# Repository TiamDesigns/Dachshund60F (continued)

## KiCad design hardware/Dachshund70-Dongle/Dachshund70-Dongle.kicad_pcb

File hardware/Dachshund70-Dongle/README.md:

# Dachshund70 2.4 GHz dongle

The receiver for the keyboard's 2.4 GHz mode (SPEC phase 14). It is a small desk puck: a USB-C cable
runs to the computer, and the puck sits on the desk near the keyboard. KiCad 10, 2 layers, 1.6 mm.

Pins come from the `dongle` section of `boards/Dachshund70/board.json`, as for the keyboard.

## Board

- 40 × 24 mm, 2 mm corners. Two unplated M2 holes, both at the USB end, so no screws sit near the antenna.
- **U2, Raytac MDBT50Q-P1MV2:** the same nRF52840 module as the keyboard, with a certified PCB antenna.
  The antenna end sits 0.4 mm inside the right edge. A keep-out covers the whole strip from the antenna
  to the edge, across the full board width, on both layers: no copper, pour or vias there.
- **J1, USB-C (HRO TYPE-C-31-M-12):** the same part as the keyboard's daughterboard. It is on the left
  edge, at the opposite end from the antenna. USB 2.0 sink: 5.1 kΩ Rd on CC1 and CC2, no PD.
- **Protection:** U1 USBLC6-2SC6 ESD clamp on D+, D− and VBUS; F1 750 mA PTC on VBUS. FB1 ties the
  receptacle shell to GND (the daughterboard does the same).
- **Power:** VBUS feeds both the module's VBUS and VDDH pins (high-voltage mode). VDD (REGOUT0) is +3V3.
  DCCH is unconnected, so REG0 runs as an LDO. There is no 32.768 kHz crystal, so firmware uses the
  internal RC oscillator. Decoupling: 4.7 µF + 100 nF on VBUS/VDDH (C1, C2) and on VDD (C3, C4).
- **User parts:**
  - SW1 PAIR: P1.06, active low.
  - SW2 RESET: P0.18.
  - D1: RGB status LED, common anode on +3V3. Red P0.08 through 1 kΩ; green P1.09 and blue P0.12
    through 330 Ω. All active low, about 1–2 mA each at standard drive.
  - The buttons sit along the top edge, with RESET on the left.
- **J2, SWD:** a 1×5 1.27 mm header in the keyboard's pin order: 1 VDD, 2 SWDIO, 3 SWDCLK, 4 nRESET,
  5 GND. Pin 1 is the probe's voltage reference. Power the dongle from USB while debugging.
- **PCA10059 compatibility:** the button and LED pins match Nordic's nRF52840 Dongle. The dongle
  firmware can be developed on a PCA10059, and the existing `nrf52840dongle/nrf52840` build target
  drives the same button and LEDs. Adafruit's `pca10059` UF2 bootloader uses P1.06 as its DFU button
  and P0.12 as an LED, so it should run here unchanged: hold PAIR while plugging in to get the UF2
  drive. This hasn't been tried yet.

### Routing

- **D+/D−:** routed by hand from U1 to the module as a side-by-side pair, about 23.5 mm each, on F.Cu
  over the B.Cu ground plane. The pair approaches the module pads from below.
- **USB-C fan-out:** no vias on the data lines. The two D+ pads are joined by a short loop under the
  receptacle body, and the two D− pads just behind the pads. U1 is flow-through: each line runs
  straight under the package between its two I/O pins.
- **Supplies:** short straight tracks, hand-routed and locked: +3V3 from C3/C4 into VDD; VDDH down to
  the VBUS row from C1/C2.
- **Everything else:** Freerouting 2.5.0, then GND pours on both layers and stitching vias. B.Cu is
  almost entirely ground.
- **Checks (kicad-cli):** ERC 0. DRC: 0 errors, 0 unconnected items, 0 schematic parity issues. Two
  warnings remain: the stock receptacle footprint's silkscreen runs past the board edge, the same as
  on the daughterboard.
- **Pin check:** a script compared every module pad with `board.json` and followed each net to its
  button, LED, resistor, SWD or USB pin: 0 mismatches.
- One +3V3 track runs on B.Cu under the D+/D− pair on its way to J2. At 12 Mbit/s this doesn't
  matter, but a re-spin could move it.

## Polling rate: 1000 Hz

The nRF52840's USB peripheral is **full speed only (12 Mbit/s)**. A full-speed interrupt endpoint can
be polled at most once per 1 ms frame (bInterval = 1), so **1000 Hz is the ceiling** for this dongle,
and for the keyboard over its own USB cable. SPEC already asks for a 1 ms interval.

The radio isn't the limit. An ESB packet at 2 Mbit/s with a ~16-byte report is about 100 µs on air,
plus 40 µs for the fast radio ramp-up. The link could carry well over 2000 reports per second.

4000 Hz or 8000 Hz would need **High-Speed USB (480 Mbit/s)**, which polls every 125 µs. That means a
different receiver chip, such as Nordic's nRF54LM20A, which has a High-Speed USB peripheral. It's out
of scope for v1, since the stack is pinned to the nRF52840.

## Keeping latency low

Rough budget for one key press over the dongle, at 1000 Hz polling and with no retransmits. These are
estimates to be measured in phase 14; SPEC already lists logic-analyser latency tests.

| Stage | Time | How to keep it low |
| --- | --- | --- |
| Detect the press | ~0.05–1 ms | When idle, drive all columns and wait for a row interrupt (GPIO SENSE), so the first press wakes the scan at once. While keys are held, scan at 1 kHz or faster. |
| Debounce | ~0 ms | Eager debounce on press (report the first edge, then ignore the key for 5 ms), deferred on release. |
| Keymap | µs | Plain keys go out at once. Tap-hold keys wait by design; keep their timeouts short. |
| Radio | ~0.15–0.2 ms | ESB at 2 Mbit/s, fast ramp-up, a short fixed report, and send immediately on change rather than on a timer. Keep the keyboard's HFXO running while keys are active (cold start costs ~0.3–0.4 ms). In dongle mode, keep BLE off so ESB has the radio to itself. |
| Retransmits | +~0.3 ms each | Short retransmit delay, a few retries, then hop to the next channel. Pick channels between the Wi-Fi channels 1, 6 and 11. |
| Dongle to USB | 0–1 ms (avg 0.5 ms) | The dongle listens all the time (it runs on USB power). Queue the report on the IN endpoint from the radio interrupt with bInterval 1. Use a small FIFO so a fast press and release in one frame isn't merged. |

**Typical total: about 1 ms, worst case about 2.5 ms without retransmits.** BLE is slower: its
connection interval is 7.5 ms at best, and many hosts use 11.25–15 ms.

What the hardware does for latency:

- **Puck on a cable, not a stick:** the puck can sit next to the keyboard, away from the computer's
  metal case and from USB 3 ports, which emit noise in the 2.4 GHz band. Fewer lost packets means fewer
  retransmits.
- **Clear antenna:** the antenna is at the board end with a full-width keep-out, and there is no metal
  near it. Use a plastic case, with no screws or labels over the antenna strip.
- **USB-powered receiver:** the dongle can keep its radio in receive and its crystal oscillator running
  all the time, with no wake-up delay.
- **Host to keyboard:** send lock LEDs and config data back as ESB ACK payloads, so the keyboard never
  needs a separate receive window.

## Bring-up checks

1. Power from USB, then check the rails: VBUS ≈ 5 V, and VDD ≈ 1.8 V on a blank module (the factory
   UICR default). Firmware must set REGOUT0 to 3.3 V, as the keyboard's `board.c` does; green and blue
   barely light at 1.8 V.
2. Flash over SWD: either the Adafruit `pca10059` UF2 bootloader (then hold PAIR while plugging in for
   the UF2 drive), or the dongle app directly.
3. Check that it enumerates as 1209:0002 "Dachshund70 Receiver", with both plug orientations and from a
   USB-C to USB-C cable (the Rd resistors).
4. Check that the LED shows red, green and blue, and that PAIR and RESET work.
5. Range and latency: measure them with the keyboard in phase 14, with the puck next to the keyboard
   and then plugged straight into a USB 3 port, to see the difference.

## Not done

- No case design yet. The case needs a light pipe over D1, button caps over SW1 and SW2, and a USB-C
  cutout. The M2 holes are a placeholder.
- 3D models: the HRO receptacle is a generated model, not HRO's (`hardware/3dmodels/`), and D1 uses KiCad's
  Würth PLCC4 3.2 × 2.8 mm RGB LED model, the same package size. Swap in the manufacturers' STEPs before
  final case work.
- A Zephyr board definition for the dongle (with the UF2 flash layout) is phase 14 work. Until then,
  CI builds the dongle app for `nrf52840dongle/nrf52840`.
- BOM: every soldered part except the SWD header has an MPN. LCSC numbers are filled in only where they
  were checked (J1, U1, R1, R2).

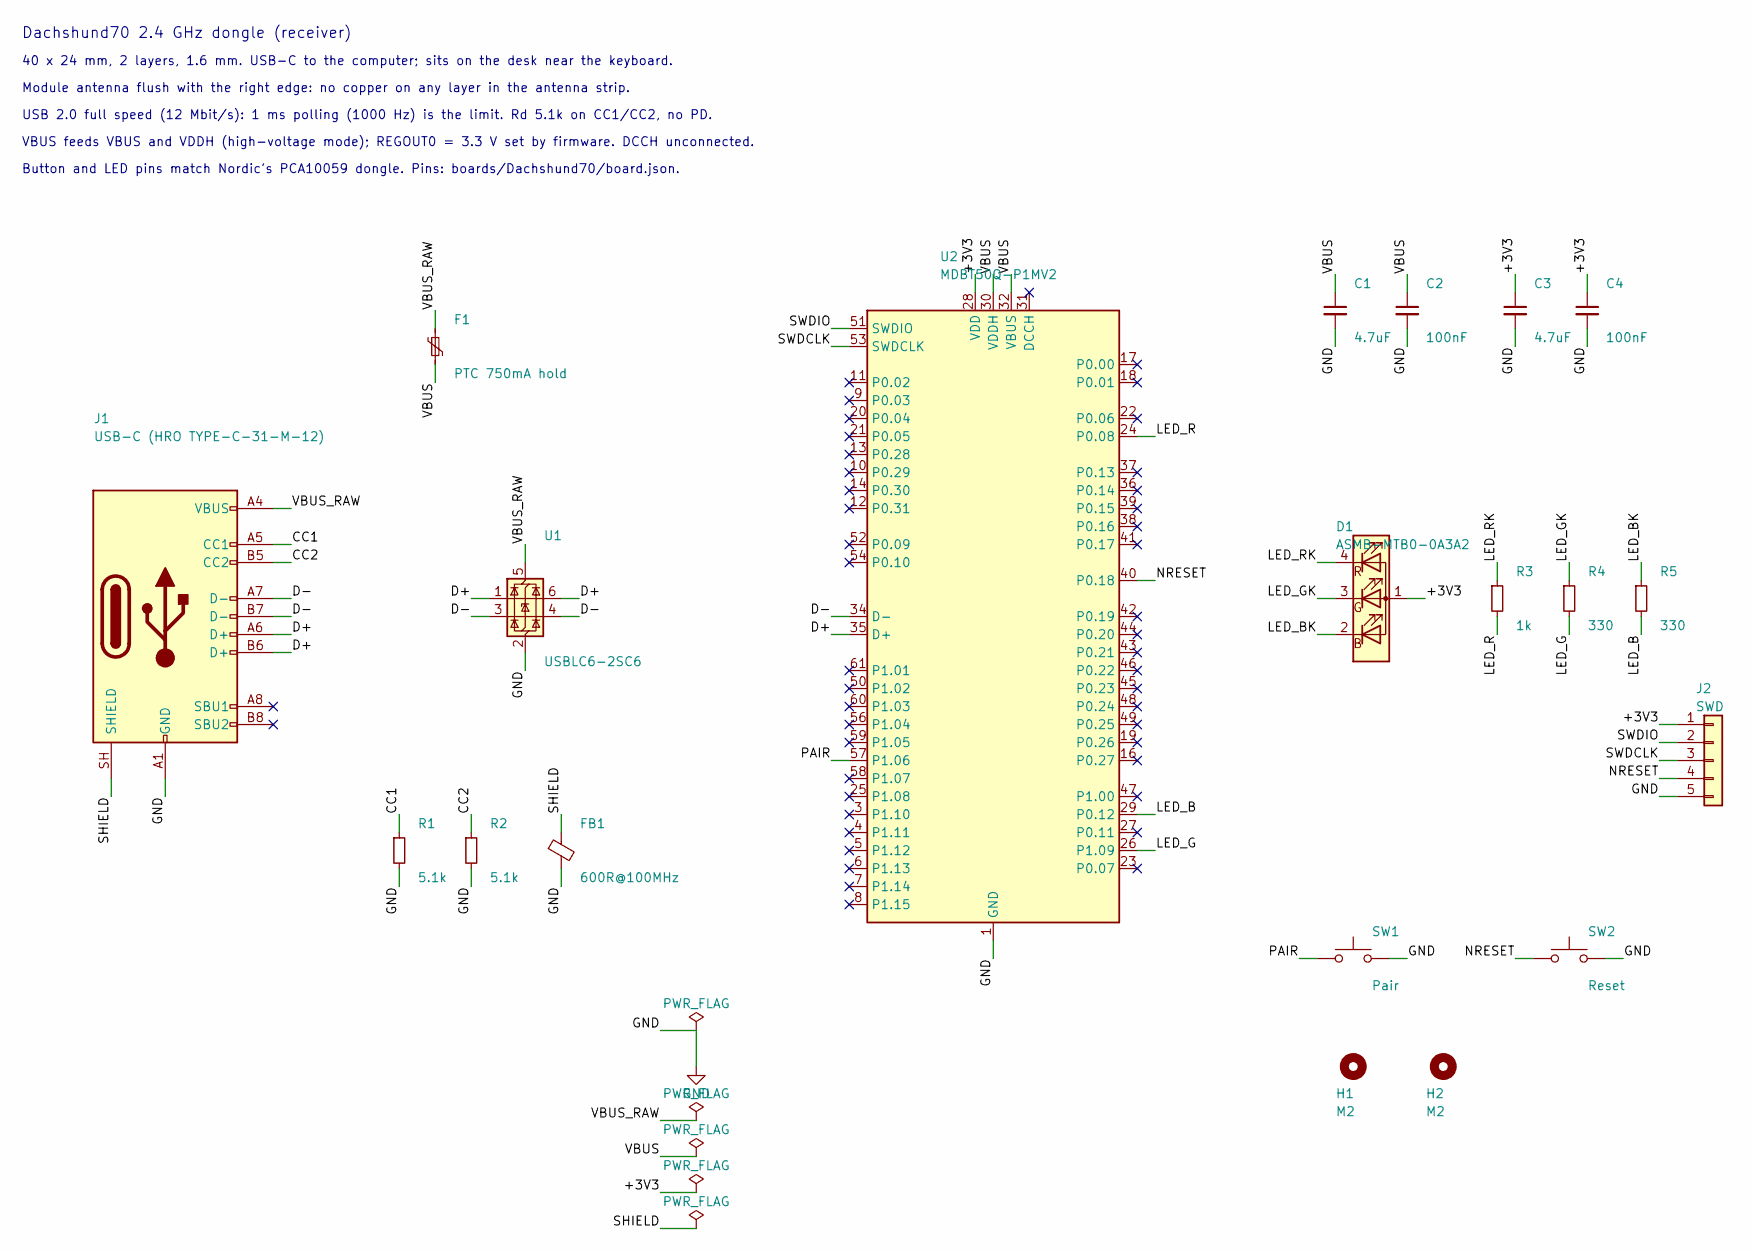
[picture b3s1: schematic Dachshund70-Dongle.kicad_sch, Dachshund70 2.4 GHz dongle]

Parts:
C1, C3: 4.7uF; C_0603_1608Metric; MPN Samsung CL10A475KO8NNNC; LCSC C19666
C2, C4: 100nF; C_0402_1005Metric; MPN Samsung CL05B104KO5NNNC; LCSC C1525
D1: ASMB-MTB0-0A3A2; LED_Avago_PLCC4_3.2x2.8mm_CW; MPN Broadcom ASMB-MTB0-0A3A2
F1: PTC 750mA hold; Fuse_1206_3216Metric; MPN BHFUSE BSMD1206-075-6V; LCSC C883127
FB1: 600R@100MHz; L_0805_2012Metric; MPN Sunlord GZ2012D601TF; LCSC C1017
H1, H2: M2; MountingHole_2.2mm_M2
J1: USB-C (HRO TYPE-C-31-M-12); USB_C_Receptacle_HRO_TYPE-C-31-M-12; MPN HRO TYPE-C-31-M-12; LCSC C165948
J2: SWD; PinHeader_1x05_P1.27mm_Vertical; MPN XFCN PZ127V-11-05-H25; LCSC C962329
R1, R2: 5.1k; R_0402_1005Metric; MPN UNI-ROYAL 0402WGF5101TCE; LCSC C25905
R3: 1k; R_0402_1005Metric; MPN UNI-ROYAL 0402WGF1001TCE; LCSC C11702
R4, R5: 330; R_0402_1005Metric; MPN UNI-ROYAL 0402WGF3300TCE; LCSC C25104
SW1: Pair; SW_SPST_TL3342; MPN E-Switch TL3342F160QG; LCSC C2886898
SW2: Reset; SW_SPST_TL3342; MPN E-Switch TL3342F160QG; LCSC C2886898
U1: USBLC6-2SC6; SOT-23-6; MPN ST USBLC6-2SC6; LCSC C7519
U2: MDBT50Q-P1MV2; Raytac_MDBT50Q; MPN Raytac MDBT50Q-P1MV2; LCSC C5119772

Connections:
/+3V3: C3.1, C4.1, D1.1 (A), J2.1, U2.28 (VDD)
/CC1: J1.A5 (CC1), R1.1
/CC2: J1.B5 (CC2), R2.1
/D+: J1.A6 (D+), J1.B6 (D+), U1.1 (I/O1), U1.6 (I/O1), U2.35 (D+)
/D-: J1.A7 (D-), J1.B7 (D-), U1.3 (I/O2), U1.4 (I/O2), U2.34 (D-)
/LED_B: R5.2, U2.29 (P0.12)
/LED_BK: D1.2 (BK), R5.1
/LED_G: R4.2, U2.26 (P1.09)
/LED_GK: D1.3 (GK), R4.1
/LED_R: R3.2, U2.24 (P0.08)
/LED_RK: D1.4 (RK), R3.1
/NRESET: J2.4, SW2.1, U2.40 (P0.18)
/PAIR: SW1.1, U2.57 (P1.06)
/SHIELD: FB1.1, J1.SH (SHIELD)
/SWDCLK: J2.3, U2.53 (SWDCLK)
/SWDIO: J2.2, U2.51 (SWDIO)
/VBUS: C1.1, C2.1, F1.2, U2.30 (VDDH), U2.32 (VBUS)
/VBUS_RAW: F1.1, J1.A4 (VBUS), J1.A9 (VBUS), J1.B4 (VBUS), J1.B9 (VBUS), U1.5 (VBUS)
GND: C1.2, C2.2, C3.2, C4.2, FB1.2, J1.A1 (GND), J1.A12 (GND), J1.B1 (GND), J1.B12 (GND), J2.5, R1.2, R2.2, SW1.2, SW2.2, U1.2 (GND), U2.1 (GND), U2.2 (GND), U2.15 (GND), U2.33 (GND), U2.55 (GND)

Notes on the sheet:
Dachshund70 2.4 GHz dongle (receiver)
40 x 24 mm, 2 layers, 1.6 mm. USB-C to the computer; sits on the desk near the keyboard.
Module antenna flush with the right edge: no copper on any layer in the antenna strip.
USB 2.0 full speed (12 Mbit/s): 1 ms polling (1000 Hz) is the limit. Rd 5.1k on CC1/CC2, no PD.
VBUS feeds VBUS and VDDH (high-voltage mode); REGOUT0 = 3.3 V set by firmware. DCCH unconnected.
Button and LED pins match Nordic's PCA10059 dongle. Pins: boards/Dachshund70/board.json.

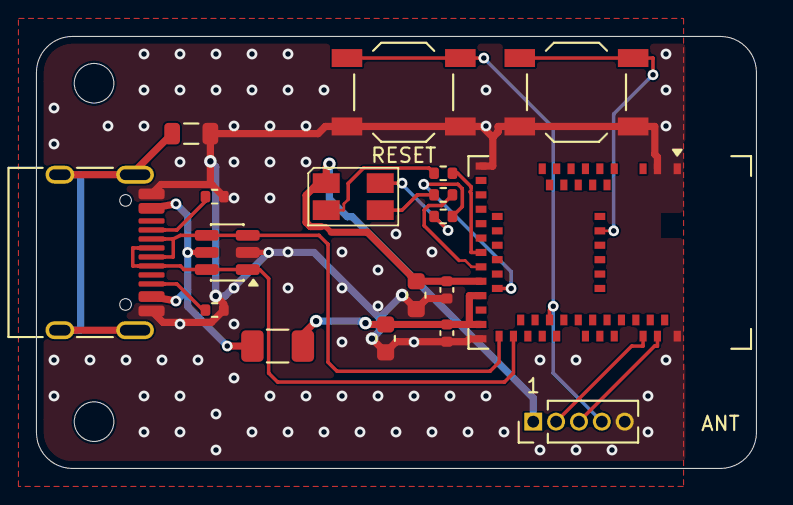
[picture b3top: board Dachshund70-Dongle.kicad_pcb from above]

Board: 2 copper layers, 40.0 x 24.0 mm, 20 parts (0 on the bottom side), 19 nets.

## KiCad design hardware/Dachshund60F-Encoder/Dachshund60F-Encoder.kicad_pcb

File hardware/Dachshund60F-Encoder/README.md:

# Dachshund60F encoder module

The roller encoder on its own small board, cabled to the mainboard. Introduced with mainboard Rev 1.1,
which no longer carries the encoder. KiCad 10 project, 2 layers, 1.6 mm FR4.

- **Encoder:** SW1, Bourns PEC12R-2220F-S0024 (shaft parallel to the board, 24 detents, 24 pulses per turn,
  20 mm shaft, push switch pressed along the shaft; LCSC C49673168, which showed no stock on 2026-10-28). Same
  body and footprint as the old SW3 (which was the 30 mm PEC12R-2230F-S0024), with the shorter shaft
  (`../3dmodels/Bourns_PEC12R-2x20F-S_standin.step`). Through-hole; its two frame tabs are on GND.
- **Cable port:** J1, JST SH 1.0 mm, 5 pins, side entry (SM05B-SRSS-TB), on the **bottom** side with the cable
  leaving at the -u edge. It plugs into the mainboard's J5 with a straight (pin 1 to pin 1) cable: a pre-made
  5-pin 1.0 mm SH cable, or SHR-05V-S housings with SSH-003T contacts.
- **Nothing else.** The 10 nF debounce capacitors on A and B and the push-switch diode D114 stay on the
  mainboard, so the pin map and the firmware did not change. No expansion ports on either board.

| J1 / J5 pin | Net | Encoder pad | MCU pin |
| --- | --- | --- | --- |
| 1 | COL14 | S1 (push switch) | matrix column 14, with diode D114 on the mainboard |
| 2 | ENC_A | A | P0.11 |
| 3 | GND | C (common) | |
| 4 | ENC_B | B | P0.12 |
| 5 | ENC_SW | S2 (push switch) | matrix row 0 through D114 |

## Geometry

Module coordinates: u runs along the shaft, toward the hub end of the board (+x of the mainboard's old
encoder); v runs across it (+y); (0, 0) is the board's top-left corner seen from above. Z is measured up
from the PCB's top face.

- Outline 22.5 (u) × 22.0 (v) mm, 1.5 mm corner radius. The right edge is the hub end of the shaft; the wheel
  starts there and the board has nothing under it.
- Encoder pad C at (15.0, 11.0). Body rear face u = 11.5, front face u = 17.5, hub to u = 22.5, shaft tip at
  u = 31.5 (20 mm shaft). Shaft axis at v = 11.0 and 10.0 mm above the PCB top.
- Two mounting holes, 2.2 mm (M2), at (2.7, 2.7) and (2.7, 19.3). The 12.5 mm-wide encoder body spans
  v 4.75 to 17.25.
- J1's pad row at u = 5.3, v = 9 to 13 (pin 1 at v = 13); its courtyard is u 0.0 to 6.6, v 6.6 to 15.4.
  The cable leaves toward -u.
- On the mainboard, J5 is on the back to the right of the corner notch: pad row at x = 331.8 mm, y = 44.5
  (pin 5) to 48.5 (pin 1), body toward -x (courtyard about x 326.9 to 333.1, y 41.9 to 51.1), cable leaving
  toward -x into the notch. The notch is open to the mainboard's top edge, x 304.0 to 326.4 mm and y 39.0 to
  57.0 mm, so the module (left edge at x 303.905) sits in it, with a 4.2 mm lobe at (306.6, 57.8) for the
  head of its lower M2 screw (its post is at y 57.82); the upper screw head is inside the notch.

## Status

DRC (kicad-cli, with schematic parity): 0 errors and 0 unconnected items. The only messages are the
library-footprint mismatch on SW1 (the board copy of the footprint is the project's own, like the mainboard's)
and the missing MPN fields that the mainboard also shows. ERC: 0. Not ordered, made or fitted.

LCSC part numbers are blank: the encoder has no LCSC listing (see PROGRESS.md, 2026-10-28), and J1's number
is still to be confirmed, so JLC would source both globally or you solder the encoder by hand.

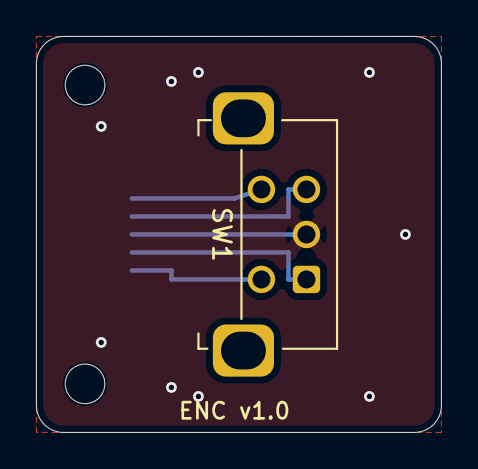
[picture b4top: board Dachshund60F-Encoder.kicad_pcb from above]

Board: 2 copper layers, 22.5 x 22.0 mm, 4 parts (1 on the bottom side), 5 nets.

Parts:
H1, H2: MountingHole_2.2mm_M2
J1: Mainboard cable; JST_SH_SM05B-SRSS-TB_1x05-1MP_P1.00mm_Horizontal
SW1: PEC12R-2220F-S0024 (shaft parallel to the board, 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; RotaryEncoder_Bourns_Horizontal_PEC12R-2x17F-Sxxxx

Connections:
/COL14: J1.1, SW1.S1
/ENC_A: J1.2, SW1.A
/ENC_B: J1.4, SW1.B
/ENC_SW: J1.5, SW1.S2
GND: J1.3, SW1.C
